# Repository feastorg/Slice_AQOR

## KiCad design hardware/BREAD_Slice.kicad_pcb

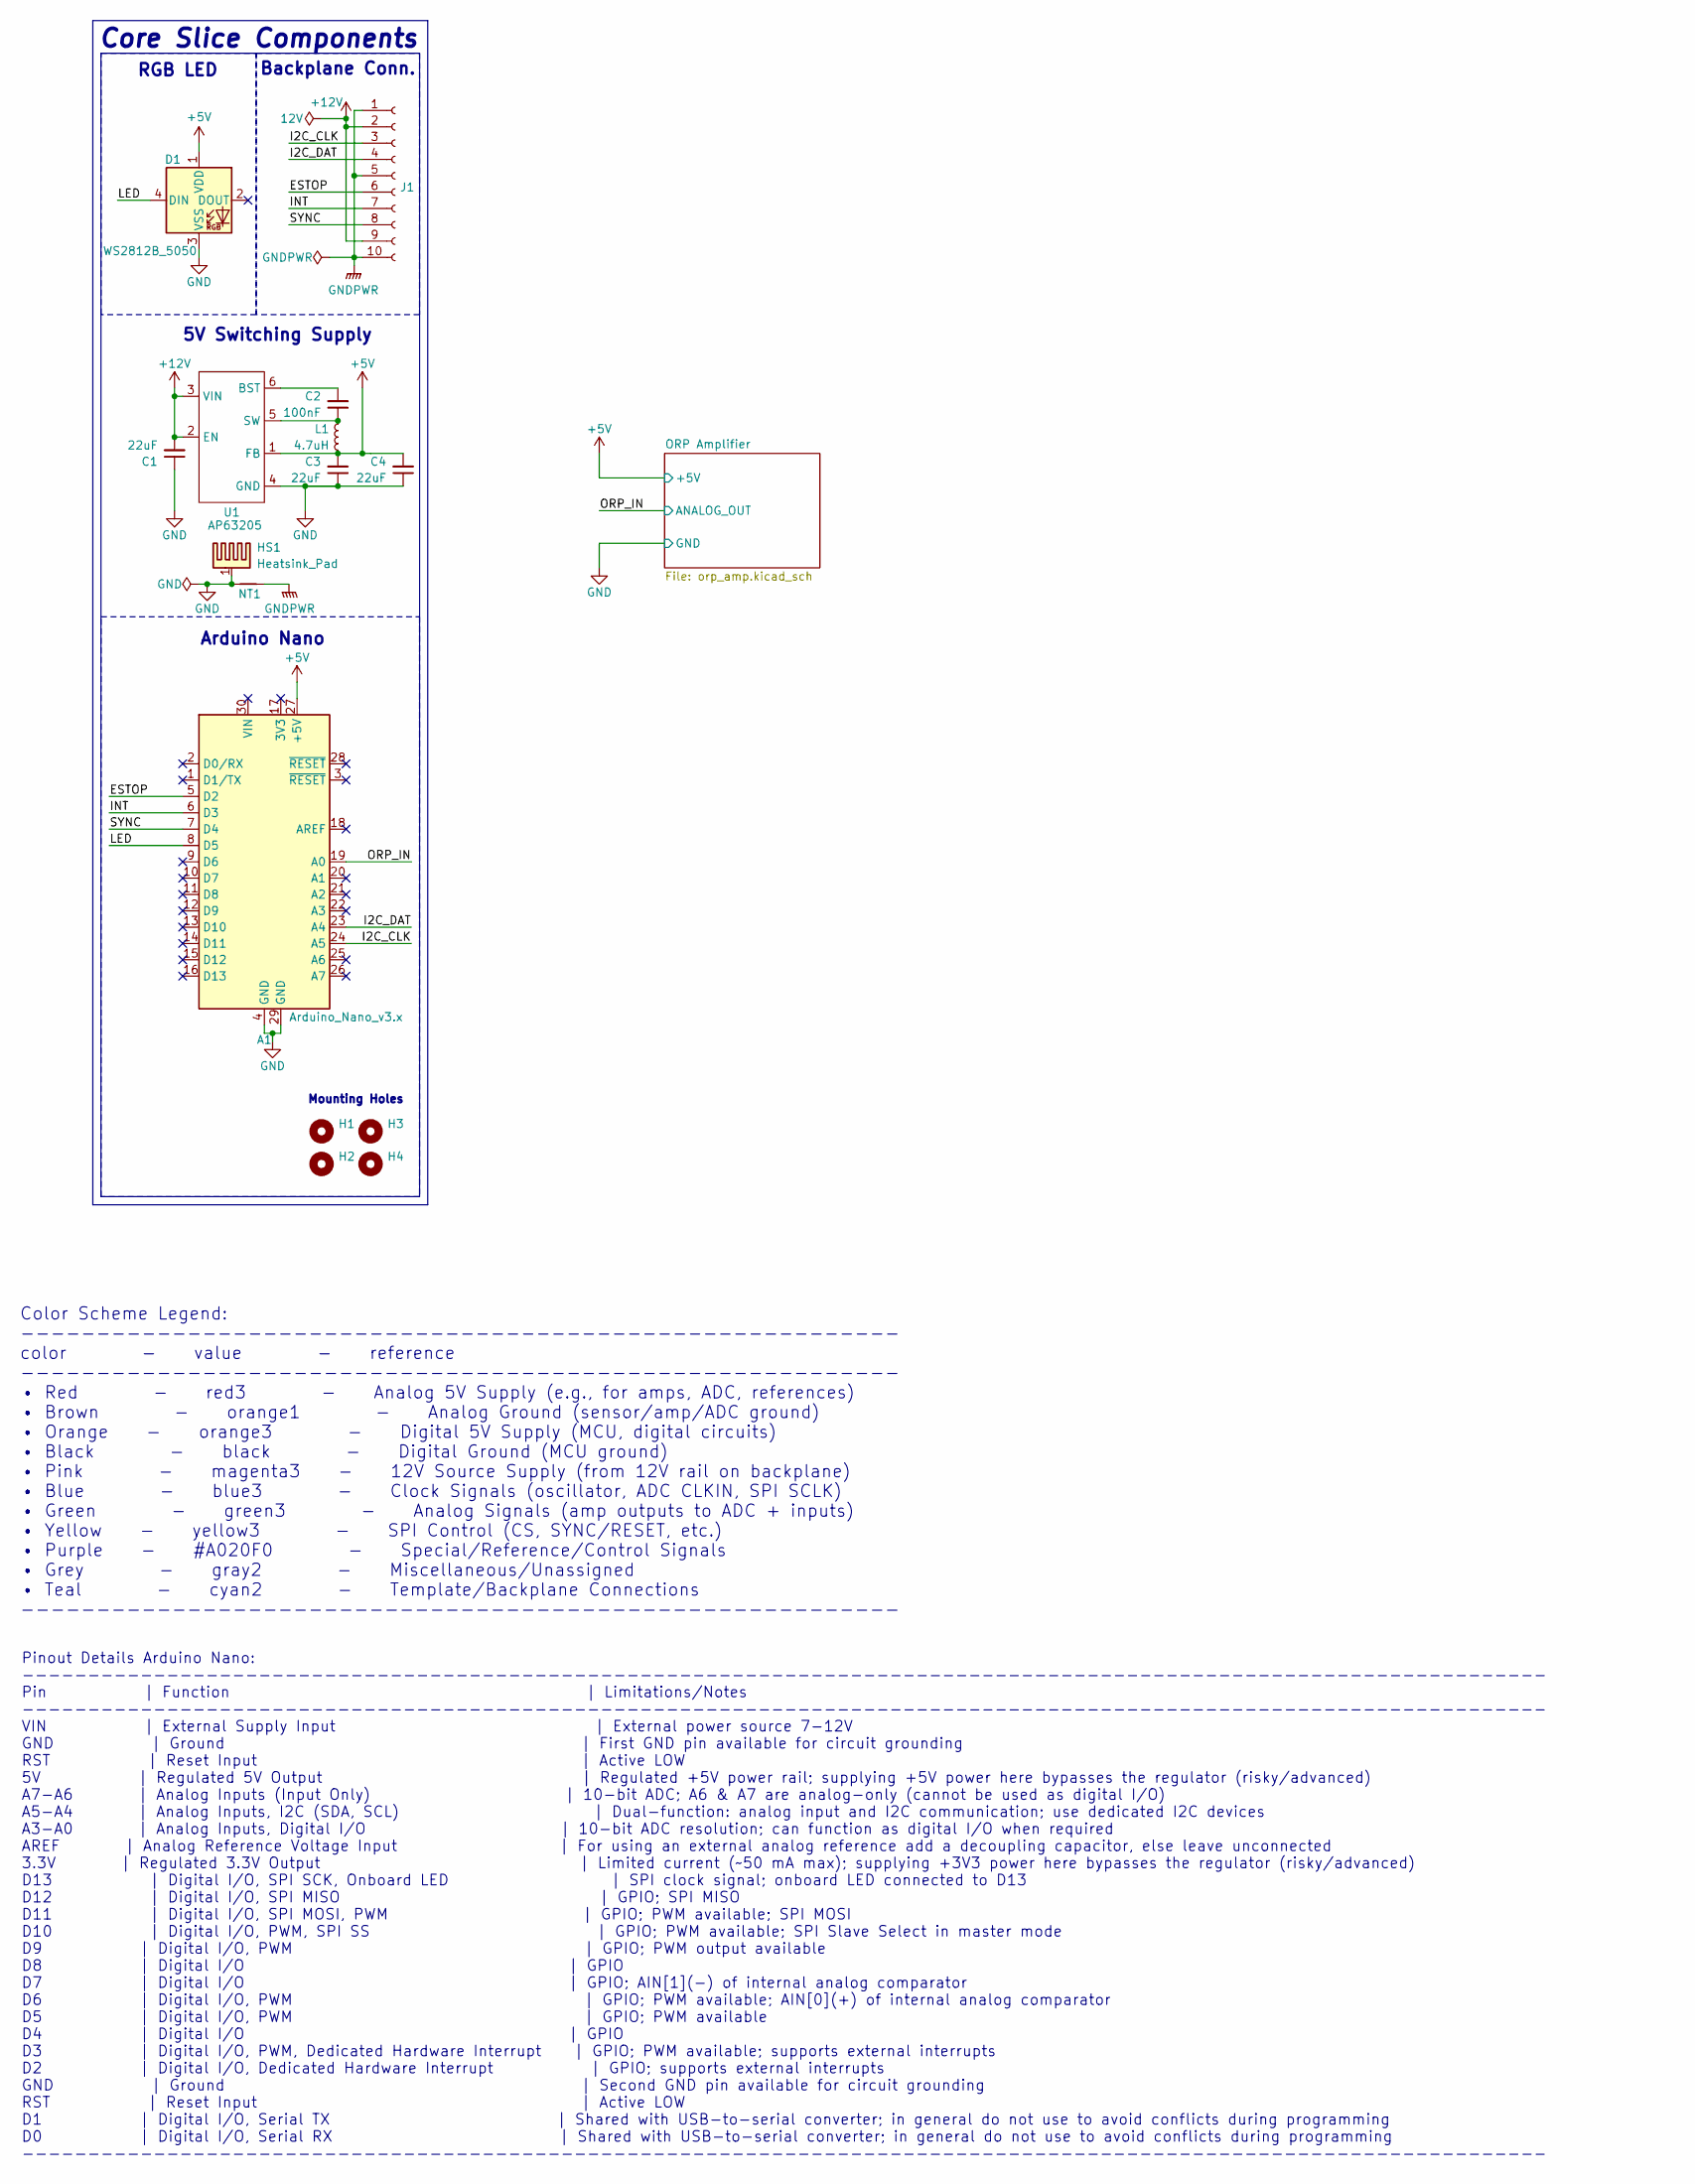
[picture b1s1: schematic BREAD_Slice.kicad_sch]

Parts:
A1: Arduino_Nano_v3.x; Arduino_Nano
C1, C3, C4: 22uF; C_1206_3216Metric
C2: 100nF; C_1206_3216Metric
D1: WS2812B_5050; WS2812-5050-4PIN
H1, H2, H3, H4: MountingHole; MountingHole_5mm
HS1: Heatsink_Pad; Thermal_Pad
J1: Conn_01x10_Female; PinSocket_1x10_P2.54mm_Horizontal
L1: 4.7uH; L_1210_3225Metric
NT1: NetTie_2; NetTie-2_SMD_Pad2.0mm
U1: AP63205; TSOT-23-6

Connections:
+5V: A1.27 (+5V), C3.2, C4.2, D1.1 (VDD), L1.2, U1.1 (FB); also elsewhere on the board
+12V: C1.2, J1.2, J1.9, U1.2 (EN), U1.3 (VIN)
/ESTOP: A1.5 (D2), J1.6
/I2C_CLK: A1.24 (A5), J1.3
/I2C_DAT: A1.23 (A4), J1.4
/INT: A1.6 (D3), J1.7
/LED: A1.8 (D5), D1.4 (DIN)
/ORP_IN: A1.19 (A0); also elsewhere on the board
/SYNC: A1.7 (D4), J1.8
GND: A1.4 (GND), A1.29 (GND), C1.1, C3.1, C4.1, D1.3 (VSS), HS1.1, NT1.1, U1.4 (GND); also elsewhere on the board
GNDPWR: J1.1, J1.5, J1.10, NT1.2
unnamed: C2.2, U1.6 (BST)
unnamed: C2.1, L1.1, U1.5 (SW)

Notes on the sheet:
5V Switching Supply
Pinout Details Arduino Nano: -------------------------------------------------------------------------------------------------------------------- Pin | Function | Limitations/Notes -------------------------------------------------------------------------------------------------------------------- V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
RGB LED
Color Scheme Legend: ---------------------------------------------------------- color - value - reference ---------------------------------------------------------- • Red - red3 - Analog 5V Supply (e.g., for amps, ADC, references) • Brown - orange1 - Analog Ground (sensor/amp/ADC ground) • Orange -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
Core Slice Components
Arduino Nano
Mounting Holes
Backplane Conn.

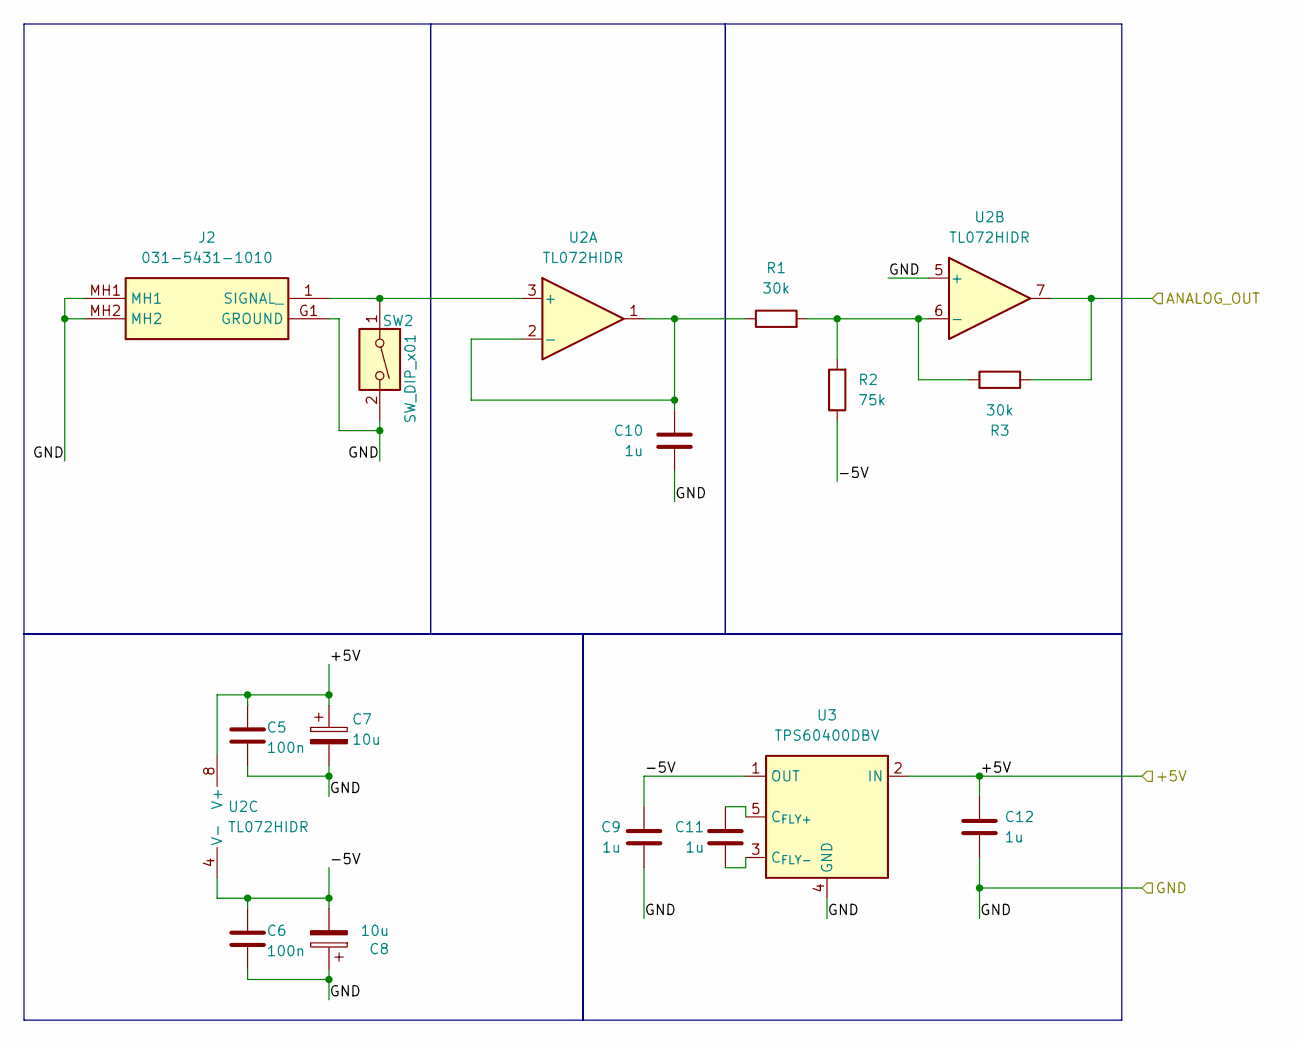
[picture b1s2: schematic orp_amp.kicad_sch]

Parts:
C5, C6: 100n; C_0805_2012Metric_Pad1.18x1.45mm_HandSolder
C7, C8: 10u; C_0805_2012Metric_Pad1.18x1.45mm_HandSolder
C9, C10, C11, C12: 1u; C_0805_2012Metric_Pad1.18x1.45mm_HandSolder
J2: 031-5431-1010; 03154311010; Mouser Part Number 523-31-5431-1010
R1, R3: 30k; R_0805_2012Metric_Pad1.20x1.40mm_HandSolder
R2: 75k; R_0805_2012Metric_Pad1.20x1.40mm_HandSolder
SW2: SW_DIP_x01; SW_DIP_SPSTx01_Slide_6.7x4.1mm_W6.73mm_P2.54mm_LowProfile_J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
U2: TL072HIDR; SOIC-8_3.9x4.9mm_P1.27mm
U3: TPS60400DBV; SOT-23-5

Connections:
+5V: C5.1, C7.1, C12.1, U2.8 (V+), U3.2 (IN); also elsewhere on the board
/ORP Amplifier/-5V: C6.1, C8.2, C9.1, R2.1, U2.4 (V-), U3.1 (OUT)
/ORP_IN: R3.1, U2.7; also elsewhere on the board
GND: C5.2, C6.2, C7.2, C8.1, C9.2, C10.1, C12.2, J2.G1 (GROUND), J2.MH1, J2.MH2, SW2.2, U2.5 (+), U3.4 (GND); also elsewhere on the board
unnamed: J2.1 (SIGNAL_), SW2.1, U2.3 (+)
unnamed: C10.2, R1.1, U2.1, U2.2 (-)
unnamed: R1.2, R2.2, R3.2, U2.6 (-)
unnamed: C11.1, U3.5 (C_{FLY+})
unnamed: C11.2, U3.3 (C_{FLY-})

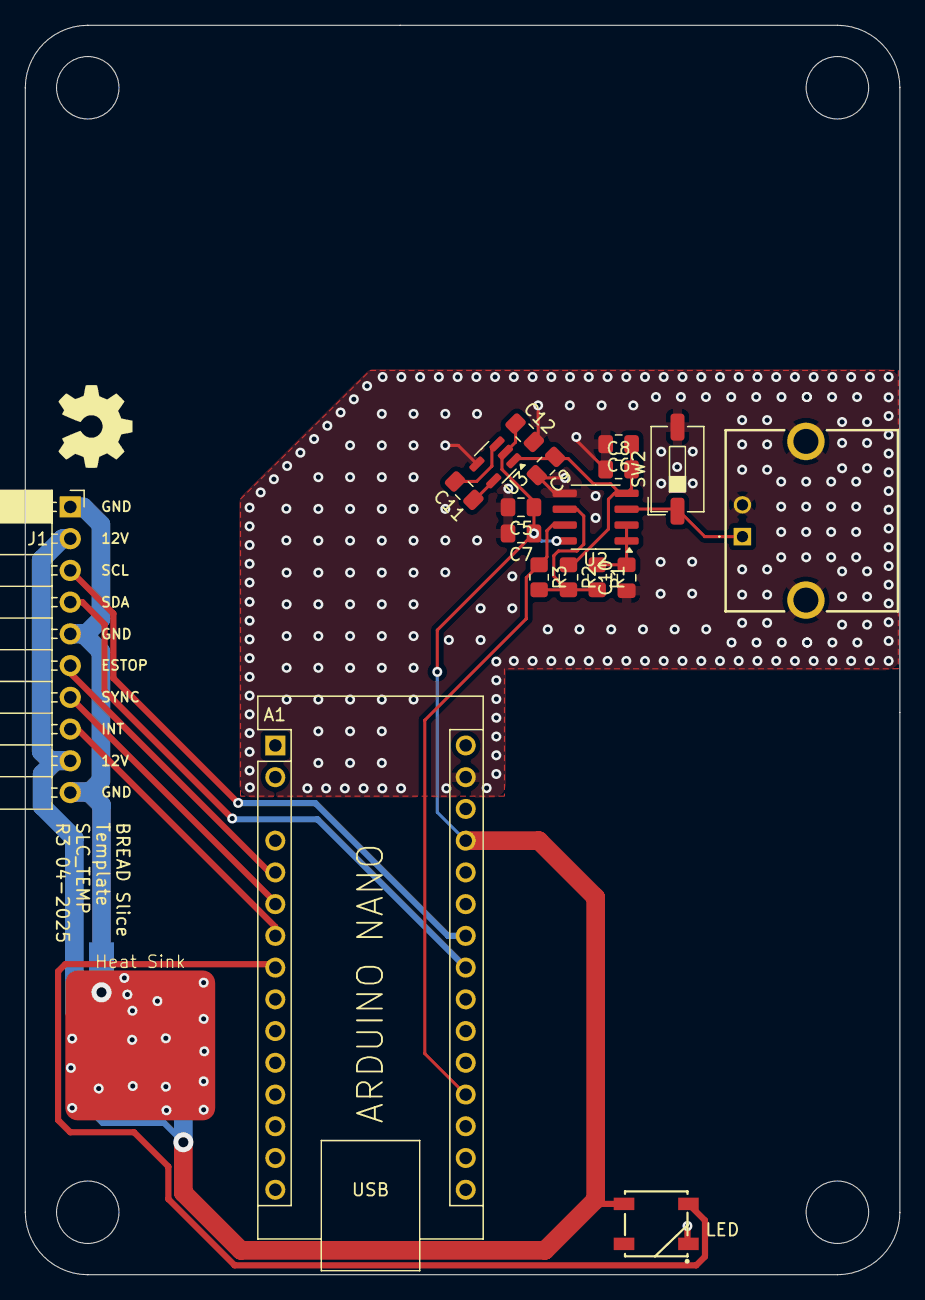
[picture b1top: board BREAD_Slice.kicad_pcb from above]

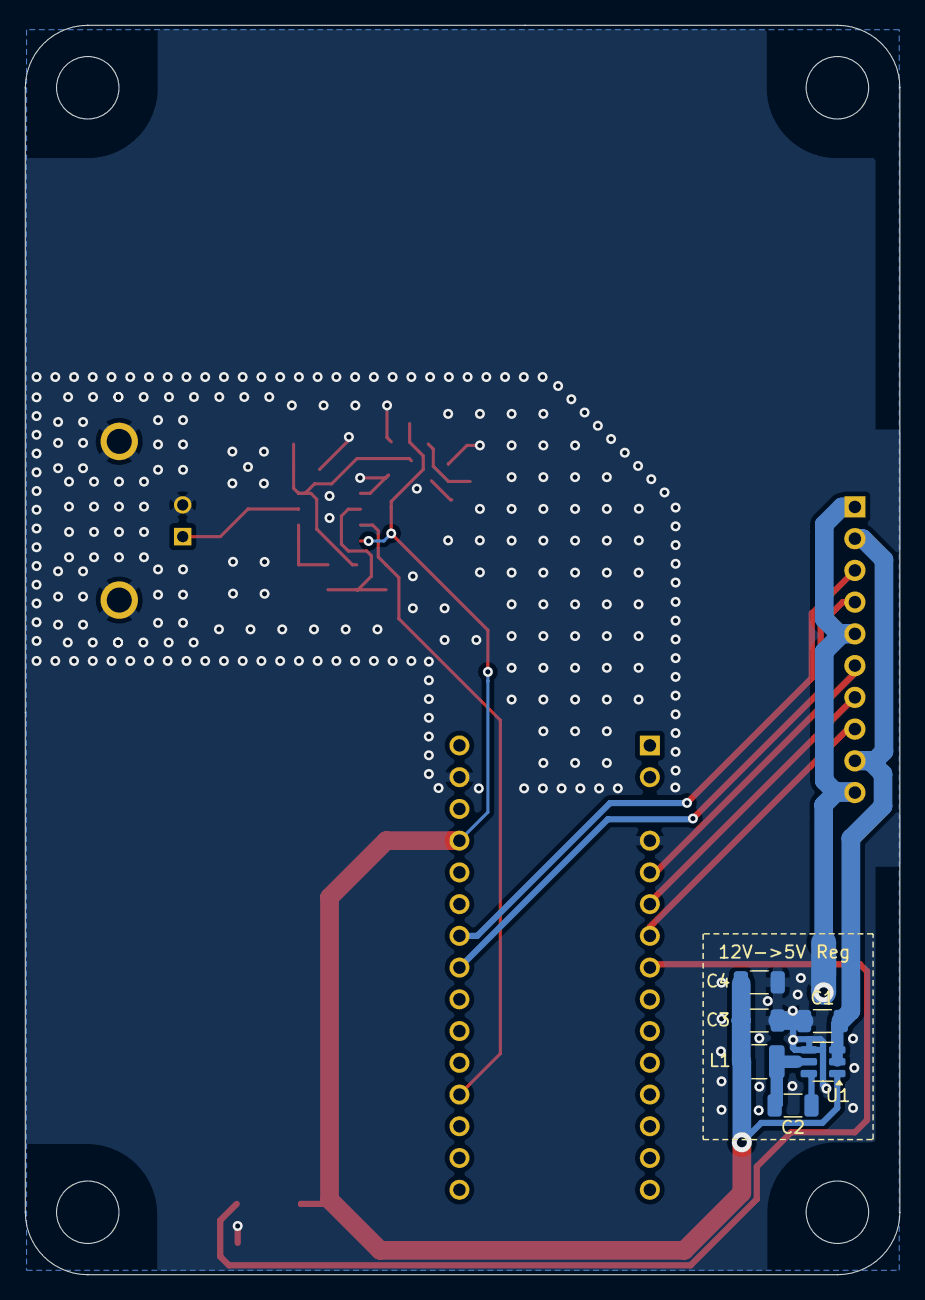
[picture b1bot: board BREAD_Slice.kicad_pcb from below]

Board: 2 copper layers, 70.0 x 100.0 mm, 31 parts (7 on the bottom side), 19 nets.

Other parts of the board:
Logo1: Logo_Open_Hardware_Small; OSHW-Symbol_6.7x6mm_SilkScreen

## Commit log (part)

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2025-04-16 initial commit, schematic and board done
2025-04-17 added to parts dump in docs
2025-04-19 minor tweaks
2026-04-18 chore: minor update
2026-05-20 Add slice.yaml manifest (schema v1.0)
2026-05-24 Add KiBot/docs pipeline
2026-05-24 📄 KiBot index + board renders (auto)
2026-05-24 TODO: all CI green
